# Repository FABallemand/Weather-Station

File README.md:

# Weather Station

## Description

This folder contains all documents needed to build a small weather station with an Arduino Nano.  
The weather station is able to track time, measure temperature and humidity. It displays everything on a small LCD screen which brightness is adjusted according to ambiant luminosity by using a LDR.

More informations: https://faballemand.github.io/html/projects/weather_station_1.html

## Components and Sensors

- AHT-10 Temperature and humidity sensor  
- HW-111 Real time clock  
- FS1000A/MX-RM-5V aka the cheapest 433MHz wireless emitter/receiver combo  
- 16x2 LCD Display  

## Repository

- **arduino:** contains various versions of the Ardiuno code  
- **pcb:** contains the Ki-CAD project for the PCB  

## Author

Fabien ALLEMAND

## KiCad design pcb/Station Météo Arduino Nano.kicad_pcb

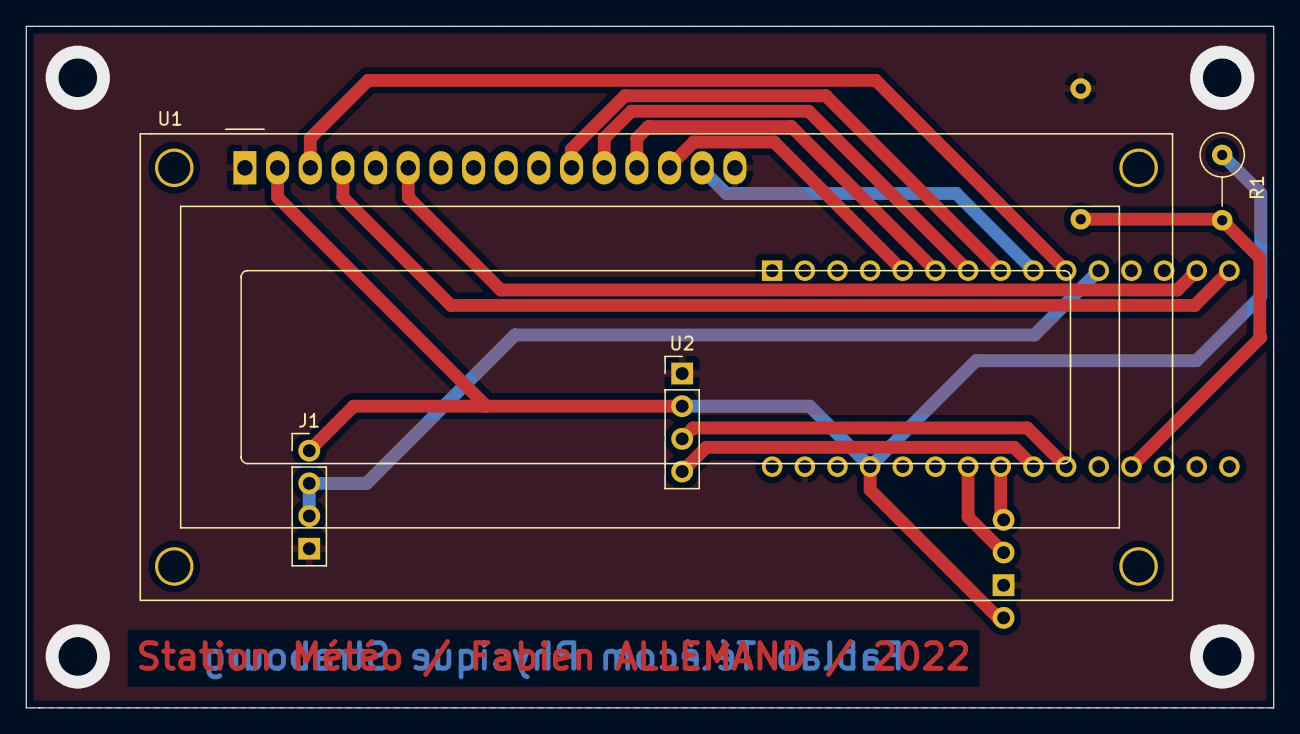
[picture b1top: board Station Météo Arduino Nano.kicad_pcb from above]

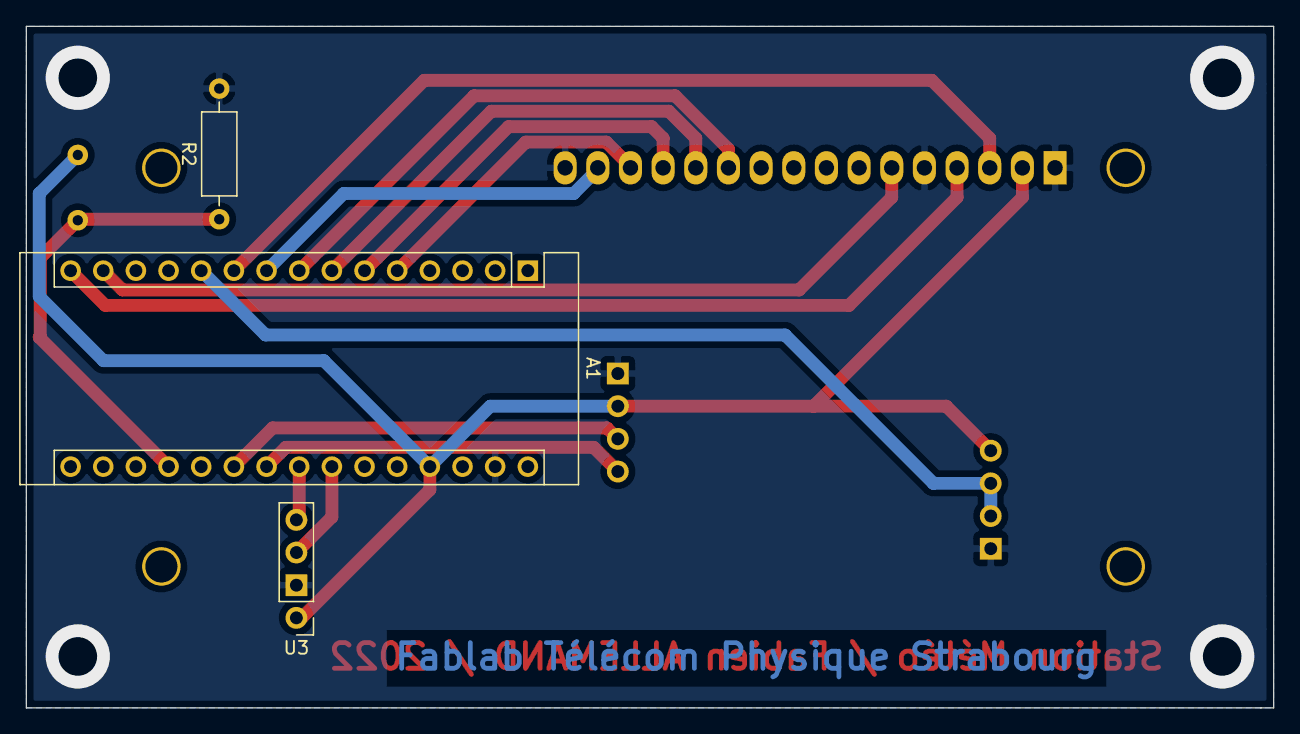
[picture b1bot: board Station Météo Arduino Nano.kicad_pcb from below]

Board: 2 copper layers, 97.0 x 53.0 mm, 7 parts (3 on the bottom side), 16 nets.

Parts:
A1: Arduino_Nano_v3.x; Arduino_Nano
J1: MX-RM-5V; PinHeader_1x04_P2.54mm_Vertical
R1: R_PHOTO; R_Axial_DIN0309_L9.0mm_D3.2mm_P5.08mm_Vertical
R2: R; R_Axial_DIN0207_L6.3mm_D2.5mm_P10.16mm_Horizontal
U1: LCD-016N002L; WC1602A
U2: HW-111; PinHeader_1x04_P2.54mm_Vertical
U3: AHT10; PinHeader_1x04_P2.54mm_Vertical

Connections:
+5V: A1.27, J1.2, R1.1, U1.2, U2.1, U3.1
AHT10_SCL: A1.24, U3.2
AHT10_SDA: A1.23, U3.3
GNDREF: A1.29, J1.4, R2.2, U1.1, U1.5, U1.16, U2.4, U3.4
HW-111_SCL: A1.22, U2.2
HW-111_SDA: A1.21, U2.3
LDR: A1.19, R1.2, R2.1
MX-RM-5V_DATA: A1.11, J1.1, J1.3
SCREEN_A: A1.9, U1.15
SCREEN_D4: A1.8, U1.11
SCREEN_D5: A1.7, U1.12
SCREEN_D6: A1.6, U1.13
SCREEN_D7: A1.5, U1.14
SCREEN_E: A1.14, U1.6
SCREEN_RS: A1.15, U1.4
SCREEN_VO: A1.10, U1.3

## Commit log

2022-10-25 second commit
2023-01-21 Modification
2023-01-21 README
